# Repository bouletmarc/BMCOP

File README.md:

# BMCOP

The BMCOP is a Coil On Plug Project made with Arduino Nano V3 for Honda/Acura running on OBD1 ecus and with a distributor.

__*This project are still in Developpement, prototyping it is completly at your own risk!*__

# Introduction

The BMCOP need 2x Signal Inputs pins to acheive triggering all the four(4x) Coils. It require 1x ICM pulse signal (usually yellow/Green wire coming out of A20/A21 output pins on the ECU) and a pulse signal coming from the FC1 header INSIDE the ecu. You'll have to get the signal from the 3rd Pins of the FC1 Header counting from the top corner of the ECU. The FC1 Header are usually in the Top Right corner in a USDM OBD1 ECU.

# Connection wiring

- On the ECU, at the FC1 header location, connect the pin1 to 5V on the arduino
- On the ECU, at the FC1 header location, connect the pin3 to D2 on the arduino
- On the ECU, at the FC1 header location, connect the pin12 to GND on the arduino
- On the ECU, at the big connectors outputs, on the big connector A, CUT the ICM wire going to the body/engine bay and connect the wire coming from the ECU connector to D3 on the arduino
- On the Arduino, connect D8 with the ICM wire previously cut going to your body (to power the tachometer)
- On the Arduino, connect D4 with the Coil1 5v signal
- On the Arduino, connect D5 with the Coil2 5v signal
- On the Arduino, connect D6 with the Coil3 5v signal
- On the Arduino, connect D7 with the Coil4 5v signal

# Parts required to assembled the Prototype PCB

- 2x 1K Ohm 1/6W Resistor
- 4x 2N4148 Diode
- 1x Arduino Nano V3 - 5V - 16Mhz

(required ONLY for the v1.2 and older)
- 2x more 1K Ohm 1/6W Resistor
- 1x 100nF (0.1uF) Capacitor
*If you want to Power the Device with 12V:*
- 1x 78M05
- 1x 1N4002 (1N4004, 2N4148 and others diodes above 20V rating will works just as fine for a replacement!)

**In the Schematic 1N4002 take place of SS12**

# Possible Issues

__*The Project is for use at your OWN COMPLETE RISK, IT HAS NOT BEING TESTED/CONFIRMED*__

The project has been updated for the V1.3 boards, which now use a different signal for syncing coils (before it was using FC1 pin4, now i've updated the project to use FC1 pin3 signal). It has not been tested personnally since I don't have any cars/engines capable of testing the project on hands, but it should be more confident this time to works arround with it.

__*If you acheive successfull results*__

I'll surely appreciate to get informed of the changes done the the programming codes or the schematic if there is any, and if you would like, you could participate in the developpement of this project by subscribing to Github and yourself 'Push updates request' to this project! I am willing to share Open Source the project I ended up with before selling the only car I could have tested on, please be kindful and let's make this a working Open Source project together.

# BMCOP V1.3 Schematic/Diagram

# BMCOP V1.2 Schematic/Diagram

[Clic HERE to Check my others Products!]:<https://bmdevs.fwscheckout.com/>

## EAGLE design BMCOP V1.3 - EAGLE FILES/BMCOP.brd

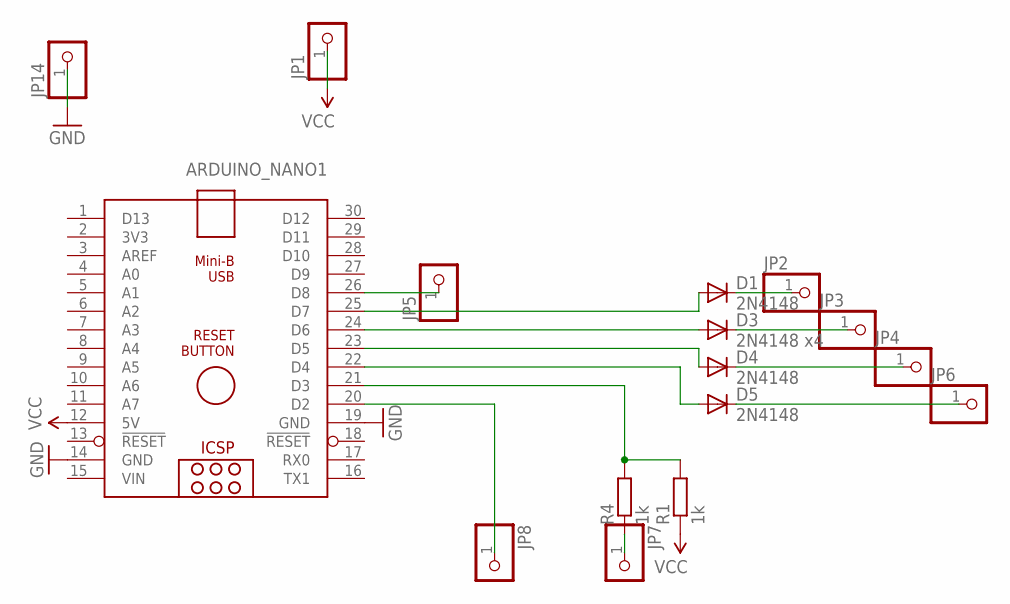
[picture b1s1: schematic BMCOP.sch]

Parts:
ARDUINO_NANO1: ARDUINO_NANO
D1, D4, D5: 2N4148; D-7.5
D3: 2N4148 x4; D-7.5
JP1, JP2, JP3, JP4, JP5, JP6, JP7, JP8, JP14: PINHD-1X1; 1X01
R1, R4: 1k; 0204/7

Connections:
GND: ARDUINO_NANO1.14 (GND), ARDUINO_NANO1.19 (GND), JP14.1
unnamed: ARDUINO_NANO1.25 (D7), D1.A
unnamed: ARDUINO_NANO1.24 (D6), D3.A
unnamed: ARDUINO_NANO1.23 (D5), D4.A
unnamed: ARDUINO_NANO1.22 (D4), D5.A
unnamed: ARDUINO_NANO1.26 (D8), JP5.1
unnamed: JP7.1, R4.1
unnamed: ARDUINO_NANO1.21 (D3), R1.2, R4.2
unnamed: D4.C, JP4.1
unnamed: D1.C, JP2.1
unnamed: D3.C, JP3.1
unnamed: ARDUINO_NANO1.20 (D2), JP8.1
unnamed: D5.C, JP6.1
VCC: ARDUINO_NANO1.12 (5V), JP1.1, R1.1
VIN: ARDUINO_NANO1.15 (VIN)

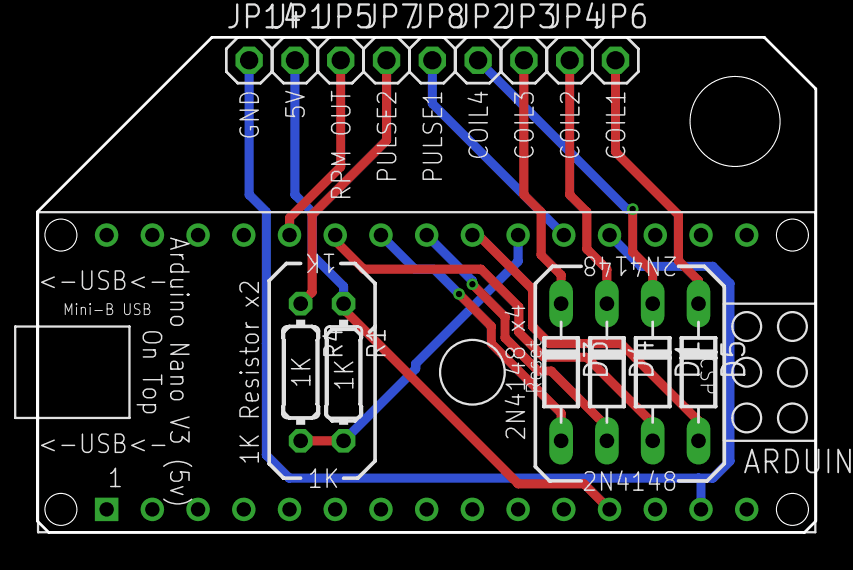
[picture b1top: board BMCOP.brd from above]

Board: 2 copper layers, 43.2 x 27.5 mm, 16 parts (0 on the bottom side), 14 nets.

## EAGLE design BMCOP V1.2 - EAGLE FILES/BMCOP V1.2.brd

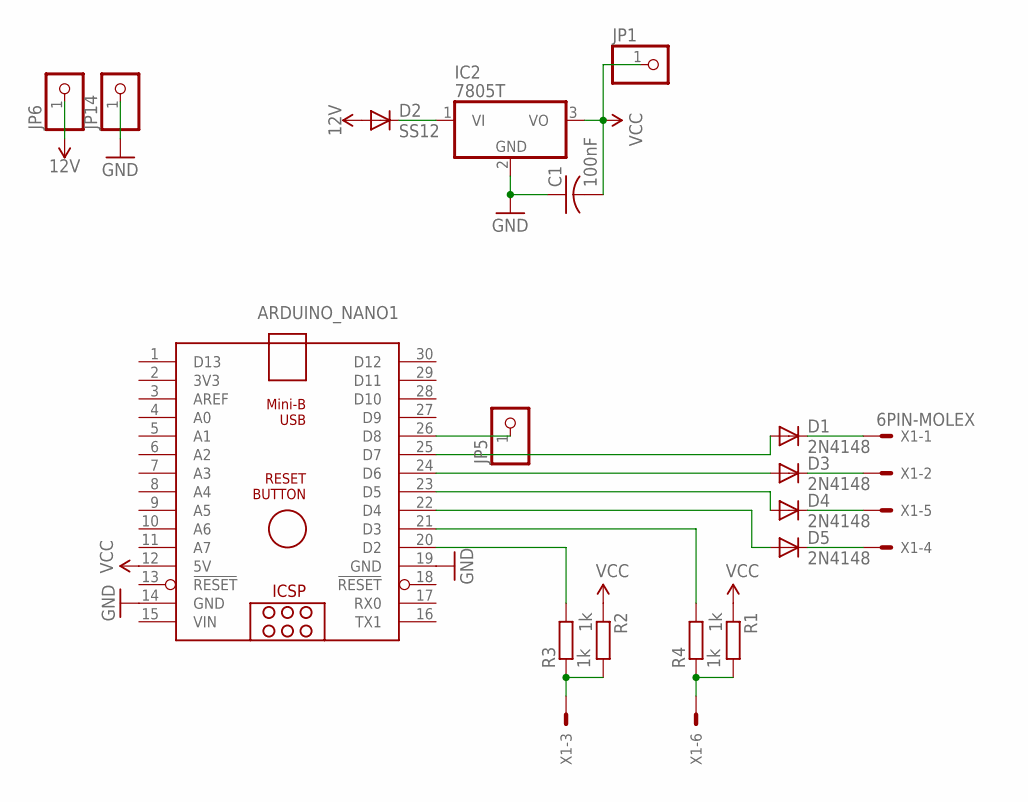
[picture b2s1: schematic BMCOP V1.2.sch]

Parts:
ARDUINO_NANO1: ARDUINO_NANO
C1: 100nF; C025-024X044
D1, D3, D4, D5: 2N4148; D-7.5
D2: SS12; D-7.5
IC2: 7805T; TO220H
JP1, JP5, JP6, JP14: PINHD-1X1; 1X01
R1, R2, R3, R4: 1k; 0204/7
X1: 6PIN-MOLEX

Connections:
12V: D2.A, JP6.1
GND: ARDUINO_NANO1.14 (GND), ARDUINO_NANO1.19 (GND), C1.1, IC2.2 (GND), JP14.1
unnamed: ARDUINO_NANO1.25 (D7), D1.A
unnamed: ARDUINO_NANO1.24 (D6), D3.A
unnamed: ARDUINO_NANO1.23 (D5), D4.A
unnamed: ARDUINO_NANO1.22 (D4), D5.A
unnamed: D2.C, IC2.1 (VI)
unnamed: ARDUINO_NANO1.26 (D8), JP5.1
unnamed: R1.2, R4.1, X1.6
unnamed: ARDUINO_NANO1.21 (D3), R4.2
unnamed: ARDUINO_NANO1.20 (D2), R3.2
unnamed: D4.C, X1.5
unnamed: D1.C, X1.1
unnamed: D3.C, X1.2
unnamed: R2.2, R3.1, X1.3
unnamed: D5.C, X1.4
VCC: ARDUINO_NANO1.12 (5V), C1.2, IC2.3 (VO), JP1.1, R1.1, R2.1
VIN: ARDUINO_NANO1.15 (VIN)

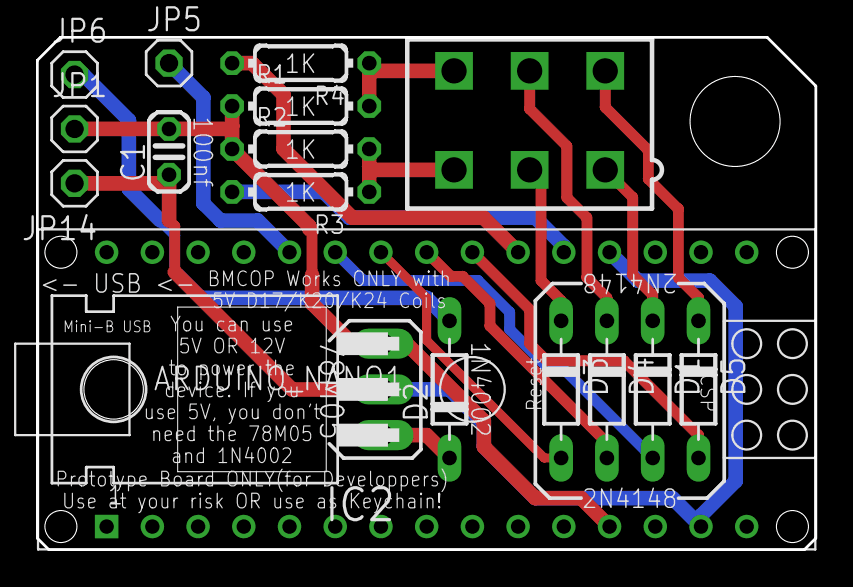
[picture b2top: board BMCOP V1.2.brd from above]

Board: 2 copper layers, 43.2 x 28.5 mm, 17 parts (0 on the bottom side), 17 nets.

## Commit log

2023-02-06 BMCOP Update file for V1.3 developement board

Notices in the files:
parts and their libraries:
SparkFun: Licensing: CC v3.0 Share-Alike You are welcome to use this library for commercial purposes.
SparkFun-PowerSymbols: Licensing: Creative Commons ShareAlike 4.0 International - https://creativecommons.org/licenses/by-sa/4.0
